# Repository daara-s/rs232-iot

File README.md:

# rs232-iot
RS-232 interface for wireless data acquisition of lab instruments using a Wemos D1 Mini microcontroller

## Goal
[Design an open source board with firmware compatible for data acquisition for a range of commonly used lab instruments](https://www.opencell.bio/summerprojects)

Initial prototyping cost: ~£10
- Wemos D1 Mini: ~£5
    - [Amazon reference](https://www.amazon.co.uk/AZDelivery-Development-ESP8266EX-Compatible-Micropython/dp/B08BTH77F3/ref=sr_1_3?dchild=1&keywords=wemos%2Bd1%2Bmini&qid=1623942509&sr=8-3&th=1)
- RS232 to TTL board: ~£5
    - [Amazon reference](https://www.amazon.co.uk/DollaTek-MAX3232-Serial-Converter-Connector/dp/B07DK3874B/ref=sr_1_3?dchild=1&keywords=rs232+to+ttl&qid=1623942563&sr=8-3)

### Roadmap
1. Research RS-232 baud rates and communication specifics of different lab instruments
2. Write a program in Arduino to confirm communication over all instrument RS-232 ports
4. Create main MQTT program to parse RS-232 data over WiFi
    * Using [EspMQTTClient](https://github.com/plapointe6/EspMQTTClient) library
5. Produce an RS-232 to TTL PCB shield for the Wemos D1 Mini using KiCAD
6. (optional) Design a 3D printed enclosure for the board in Fusion 360

### Other considerations
- Power: LiPo batteries vs USB vs wall socket
- integrating into existing [OpenCell fermentrack](https://github.com/tmopencell/sudo.bio) system

### RS-232 Shield
Shield board for the Wemos D1 Mini

### References
[Seeedstudio RS-232 to TTL converter](https://wiki.seeedstudio.com/RS-232_To_TTL_Conveter-MAX3232IDR/)
- licensed under: https://creativecommons.org/licenses/by/4.0/

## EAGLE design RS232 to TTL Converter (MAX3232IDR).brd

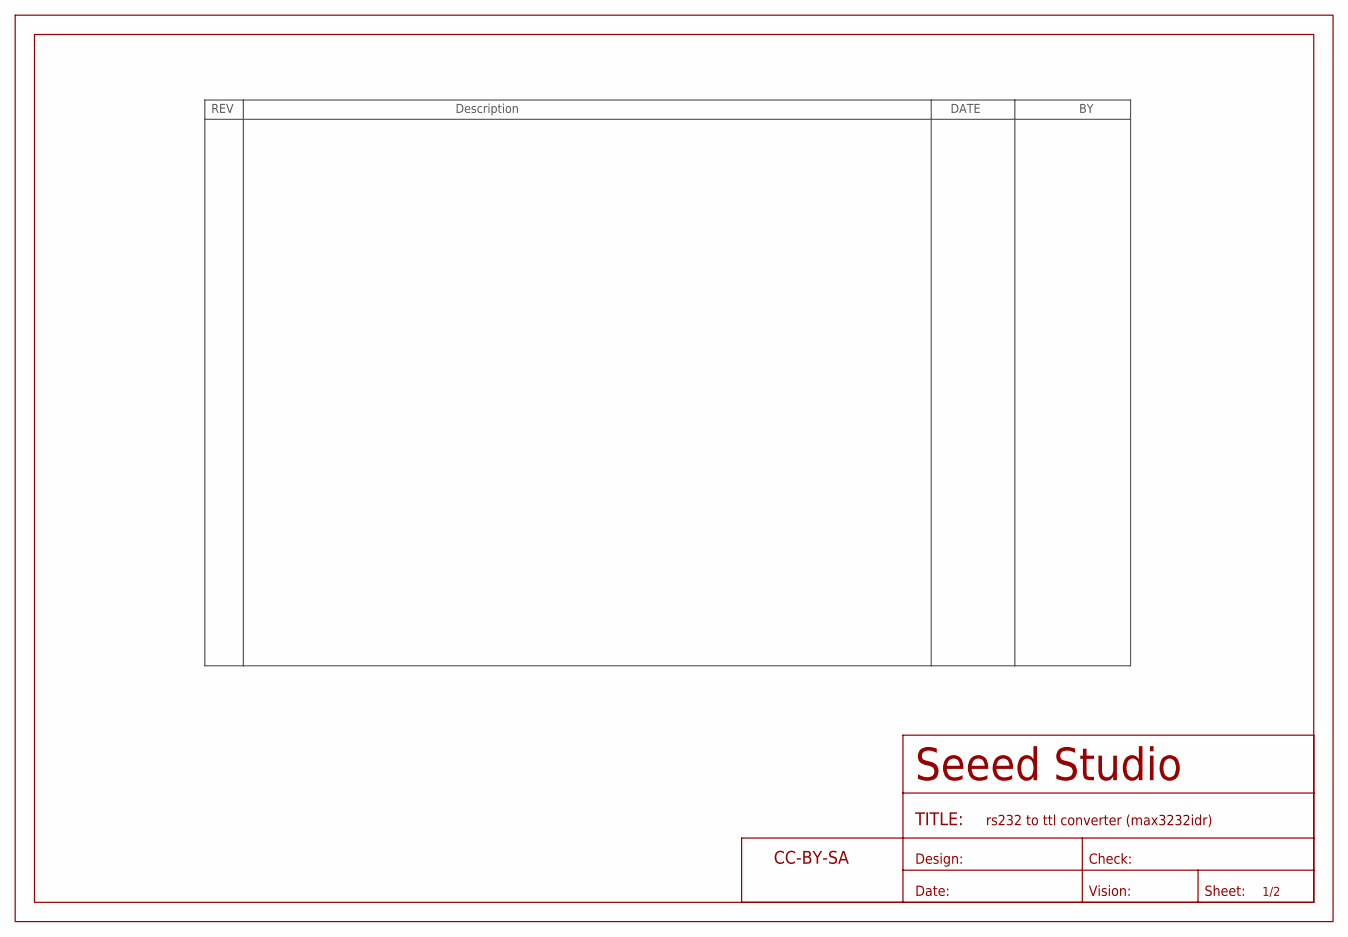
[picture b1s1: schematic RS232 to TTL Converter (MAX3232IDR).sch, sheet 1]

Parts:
FR1: SEEEDSTUDIO-OPEN-SCH-FRAME; SEEEDSTUDIO-PCB-FRAME

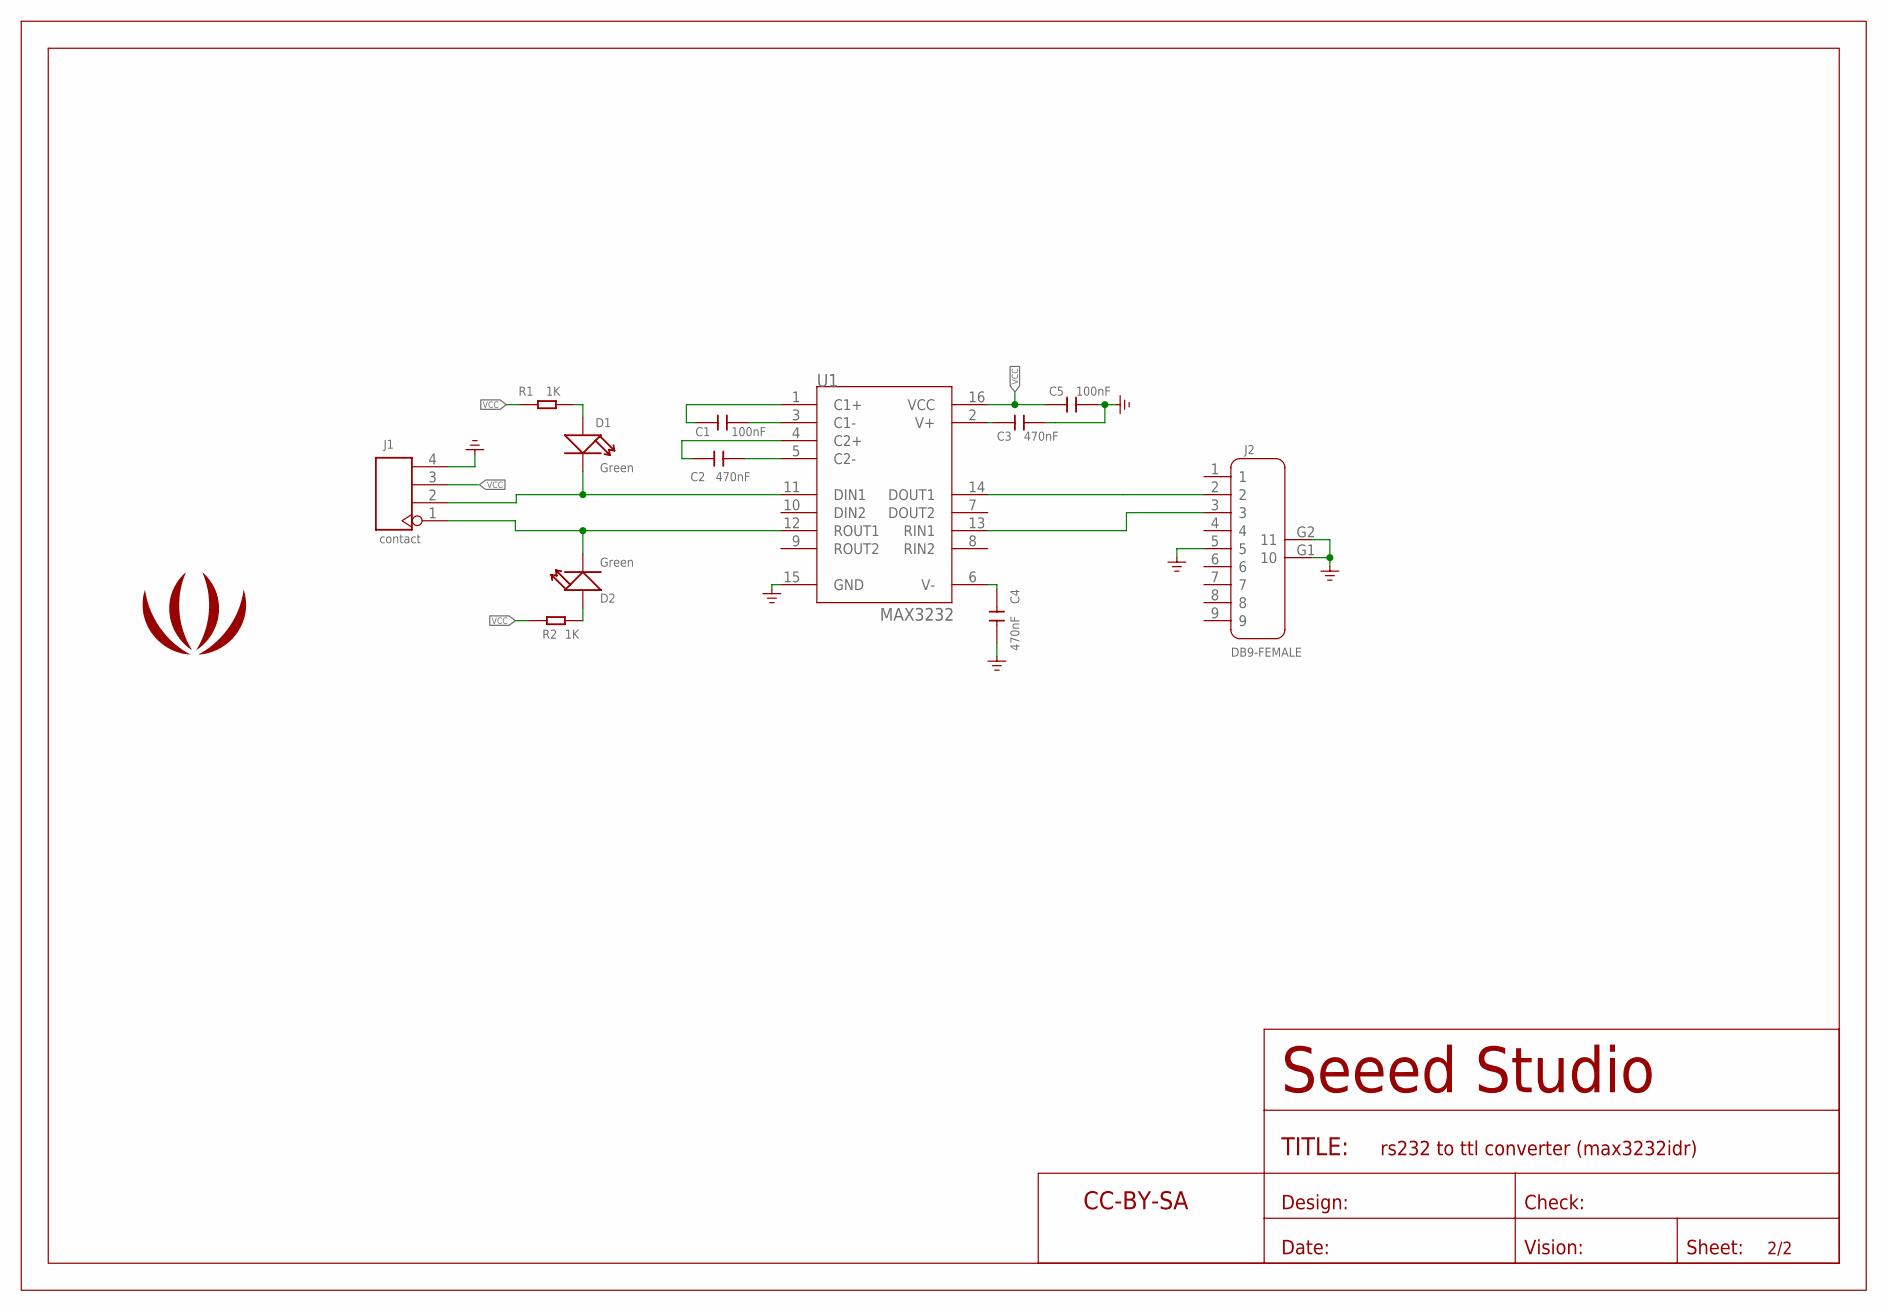
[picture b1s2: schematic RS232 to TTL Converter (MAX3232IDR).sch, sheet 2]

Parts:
C1, C5: 100nF; C0603
C2, C3, C4: 470nF; C0603
D1, D2: Green; LED-0603
FR2: SEEEDSTUDIO-OPEN-SCH-FRAME; SEEEDSTUDIO-PCB-FRAME
J1: contact; H4-2.54
J2: DB9-FEMALE; DSUB9+2P-2.77-90D-FEMALE
R1, R2: 1K; R0603
U1: MAX3232; SOIC16-1.27-10X3.9MM
U$2: LOGO-SEEED-BIG-SILK; SEEED-SILK-280*268MIL

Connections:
232-RXD: J2.3, U1.13 (RIN1)
232-TXD: J2.2, U1.14 (DOUT1)
GND: C3.2, C4.2, C5.2, J1.4, J2.5, J2.G1 (10), J2.G2 (11), U1.15 (GND)
unnamed: C1.2, U1.1 (C1+)
unnamed: C1.1, U1.3 (C1-)
unnamed: C2.2, U1.4 (C2+)
unnamed: C2.1, U1.5 (C2-)
unnamed: C3.1, U1.2 (V+)
unnamed: C4.1, U1.6 (V-)
unnamed: D1.+, R1.1
unnamed: D2.+, R2.2
unnamed: D1.-, J1.2, U1.11 (DIN1)
unnamed: D2.-, J1.1, U1.12 (ROUT1)
VCC: C5.1, J1.3, R1.2, R2.1, U1.16 (VCC)

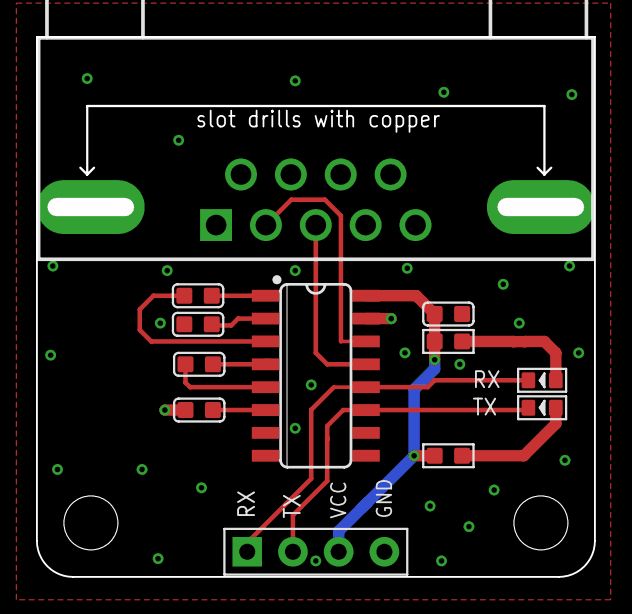
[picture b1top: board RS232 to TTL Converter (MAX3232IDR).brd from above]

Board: 2 copper layers, 30.1 x 29.1 mm, 15 parts (1 on the bottom side), 14 nets.

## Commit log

2021-06-17 Add RS232 to TTL schematic and board layout
    Source: https://wiki.seeedstudio.com/RS-232_To_TTL_Conveter-MAX3232IDR/
2021-06-17 Rename RS232 to TTL Converter (MAX3232IDR).brd to rs232/RS232 to TTL Converter (MAX3232IDR).brd
2021-06-17 Rename RS232 to TTL Converter (MAX3232IDR).sch to rs232/RS232 to TTL Converter (MAX3232IDR).sch
2021-06-17 Add consideration of existing fermentrack system
    Also add goal link
2021-06-18 Add RS-232 serial passthrough program
    Allows parsing data directly to the serial monitor, allowing for debugging and building MQTT program
2021-06-18 Change MQTT libary
2021-06-18 Add MQTT client template
    Program to be modified after testing with RS-232 passthrough
2021-06-18 Add references section
    Moved schematic to references section
2021-06-19 Add RS-232 Shield Schematic
    Schematic for an RS-232 shield to mount on a Wemos D1 Mini board via headers
2021-06-19 Reorganise folder structure, add shield schematic image
2021-06-20 Add RS-232 Shield PCB layout
2021-07-06 Modify PCB silkscreens
    Project-specific footprint added for Wemos D1 Mini
2021-07-06 Add board name to silkscreen

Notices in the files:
parts and their libraries:
moudle-new: This work is licensed under the Creative Commons Attribution 4.0 International License.
To view a copy of this license,visit:
http://creativecommons.org/licenses/by-sa/4.0
moudle-new: CC-BY-SA
